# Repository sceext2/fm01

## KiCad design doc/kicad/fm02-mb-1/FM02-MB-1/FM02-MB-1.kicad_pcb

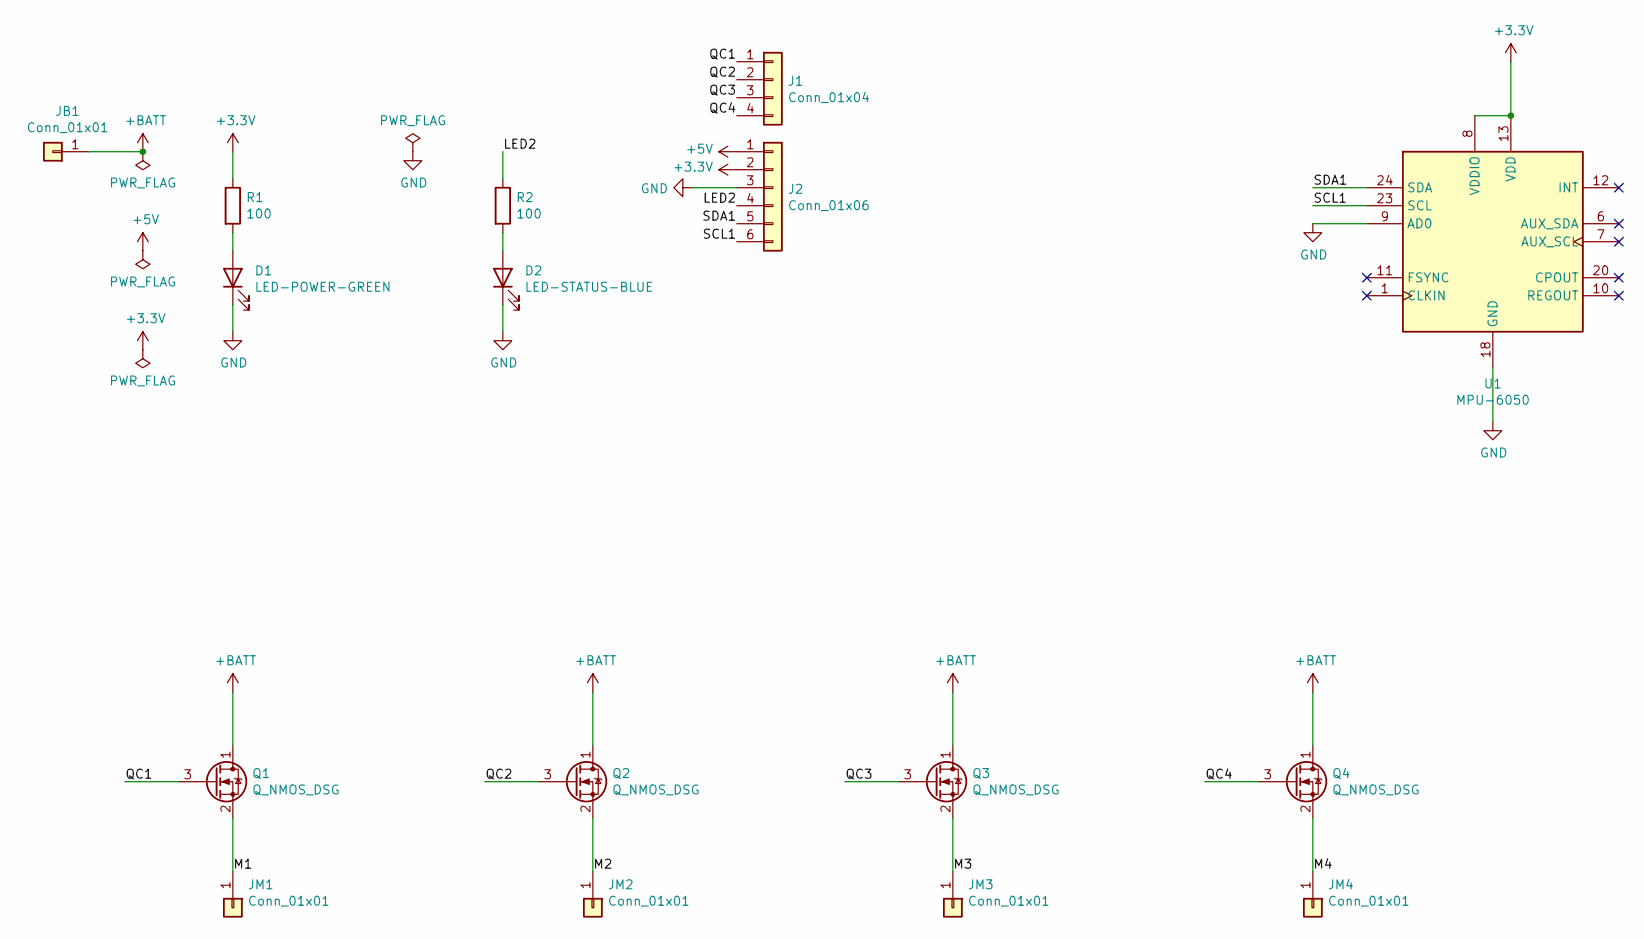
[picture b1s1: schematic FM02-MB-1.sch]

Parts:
D1: LED-POWER-GREEN; LED_0402_1005Metric
D2: LED-STATUS-BLUE; LED_0402_1005Metric
J1: Conn_01x04; CSMD-J4P
J2: Conn_01x06; CSMD-J6P
JB1: Conn_01x01; CSMD-JBATT
JM1, JM2, JM3, JM4: Conn_01x01; CSMD-JM2
Q1, Q2, Q3, Q4: Q_NMOS_DSG; TO-252-2
R1, R2: 100; R_0402_1005Metric
U1: MPU-6050; InvenSense_QFN-24_4x4mm_P0.5mm

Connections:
+3V3: J2.2, R1.1, U1.8 (VDDIO), U1.13 (VDD)
+5V: J2.1
+BATT: JB1.1, Q1.1 (D), Q2.1 (D), Q3.1 (D), Q4.1 (D)
/LED2: J2.4, R2.1
/M1: JM1.1, Q1.2 (S)
/M2: JM2.1, Q2.2 (S)
/M3: JM3.1, Q3.2 (S)
/M4: JM4.1, Q4.2 (S)
/QC1: J1.1, Q1.3 (G)
/QC2: J1.2, Q2.3 (G)
/QC3: J1.3, Q3.3 (G)
/QC4: J1.4, Q4.3 (G)
/SCL1: J2.6, U1.23 (SCL)
/SDA1: J2.5, U1.24 (SDA)
GND: D1.1 (K), D2.1 (K), J2.3, U1.9 (AD0), U1.18 (GND)
unnamed: D1.2 (A), R1.2
unnamed: D2.2 (A), R2.2

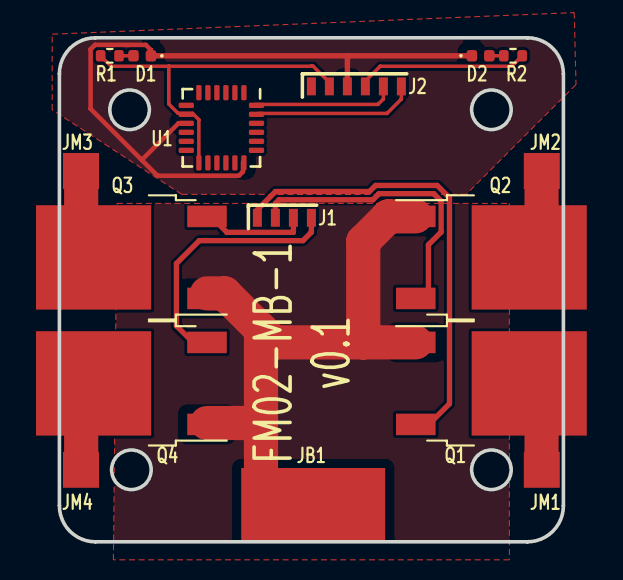
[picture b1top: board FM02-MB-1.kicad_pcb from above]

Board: 2 copper layers, 28.0 x 28.0 mm, 16 parts (0 on the bottom side), 16 nets.

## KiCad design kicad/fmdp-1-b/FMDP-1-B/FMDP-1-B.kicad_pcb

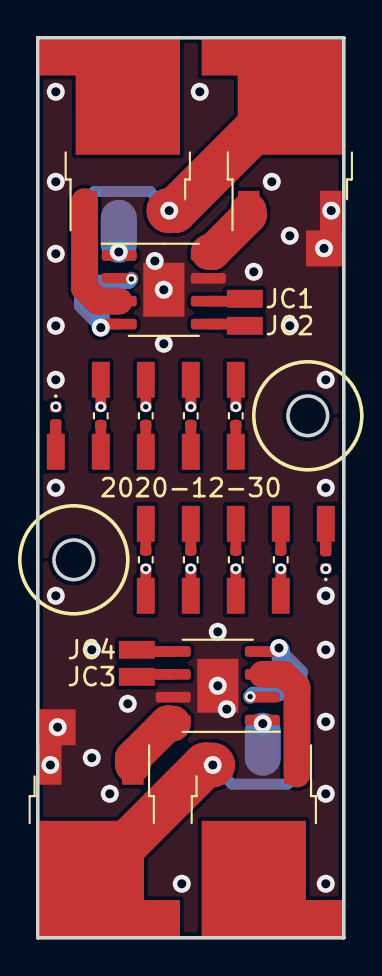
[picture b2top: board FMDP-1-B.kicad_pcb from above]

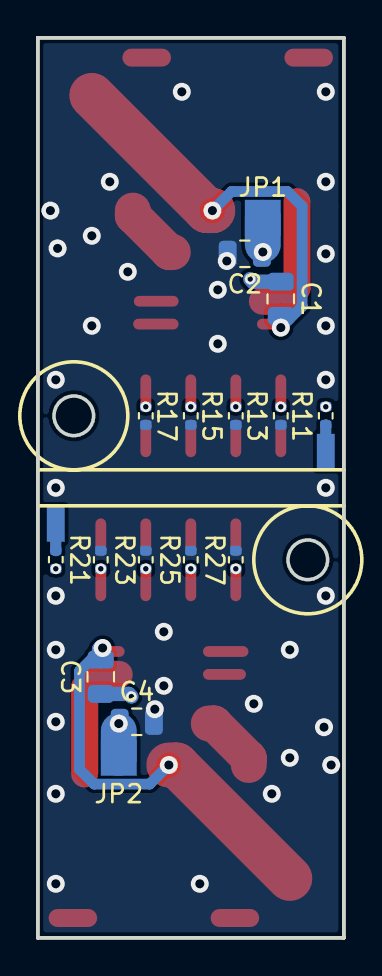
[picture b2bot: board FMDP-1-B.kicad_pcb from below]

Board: 2 copper layers, 17.0 x 50.0 mm, 62 parts (18 on the bottom side), 39 nets.

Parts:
C1, C3: 0.1u 100V; C_0805_2012Metric
C2, C4: 10u 25V; C_0805_2012Metric
D1, D2: LED; LED_0402_1005Metric
J1, J2, J3, J4: Conn_01x01; JS-2x2mm
JC1, JC2, JC3, JC4: Conn_01x01; JS-1x2mm
JG1, JG2: Conn_01x01; JS-2x2mm
JL1, JL2: Conn_01x01; JS-1x2mm
JP1, JP2: Conn_01x01; JS-2x2mm
JS11, JS12, JS13, JS14, JS15, JS16, JS17, JS18, JS21, JS22, JS23, JS24, JS25, JS26, JS27, JS28: Conn_01x01; JS-1x2mm
JV1, JV2: Conn_01x01; JS-1x2mm
Q1, Q2, Q3, Q4: AOD482; TO-252-2
R1, R2: 100?; R_0402_1005Metric
R11, R14, R16, R18, R21, R24, R26, R28: 3.3k; R_0402_1005Metric
R12, R22: 100k; R_0402_1005Metric
R13, R15, R17, R23, R25, R27: 4.7k; R_0402_1005Metric
U1, U2: UCC27211; SOIC-8-1EP_3.9x4.9mm_P1.27mm_EP2.29x3mm

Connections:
/B1/HI: JC2.1, U1.5
/B1/HO: Q2.1, U1.3
/B1/HS: C1.2, J1.1, Q1.2, Q2.3, U1.4
/B1/LI: JC1.1, U1.6
/B1/LO: Q1.1, U1.8
/B1/VDD: C2.1, JP1.1, U1.1
/B1/VH: J2.1, Q2.2
/B2/HI: JC4.1, U2.5
/B2/HO: Q4.1, U2.3
/B2/HS: C3.2, J3.1, Q3.2, Q4.3, U2.4
/B2/LI: JC3.1, U2.6
/B2/LO: Q3.1, U2.8
/B2/VDD: C4.1, JP2.1, U2.1
/B2/VH: J4.1, Q4.2
GND: C2.2, C4.2, JG1.1, JG2.1, Q1.3, Q3.3, R11.2, R13.2, R15.2, R17.2, R21.2, R23.2, R25.2, R27.2, U1.7, U1.9, U2.7, U2.9
unnamed: C1.1, U1.2
unnamed: C3.1, U2.2
unnamed: D1.1, R1.1
unnamed: D1.2, JV1.1
unnamed: D2.1, R2.1
unnamed: D2.2, JV2.1
unnamed: JL1.1, R1.2
unnamed: JL2.1, R2.2
unnamed: JS11.1, R11.1, R12.2
unnamed: JS12.1, R12.1
unnamed: JS13.1, R13.1, R14.2
unnamed: JS14.1, R14.1
unnamed: JS15.1, R15.1, R16.2
unnamed: JS16.1, R16.1
unnamed: JS17.1, R17.1, R18.2
unnamed: JS18.1, R18.1
unnamed: JS21.1, R21.1, R22.2
unnamed: JS22.1, R22.1
unnamed: JS23.1, R23.1, R24.2
unnamed: JS24.1, R24.1
unnamed: JS25.1, R25.1, R26.2
unnamed: JS26.1, R26.1
unnamed: JS27.1, R27.1, R28.2
unnamed: JS28.1, R28.1
